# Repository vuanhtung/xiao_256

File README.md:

# xiao_256

Split keyboard with 5 rows & 6 columns on each half (hence the name 2 * 5 * 6) using xiao ble mcu & gateron low profile switch.

The pcb is reversible. A small pcb is also available to cover the mcu, the battery, & the wiring.

zmk config is available at https://github.com/vuanhtung/zmk-config

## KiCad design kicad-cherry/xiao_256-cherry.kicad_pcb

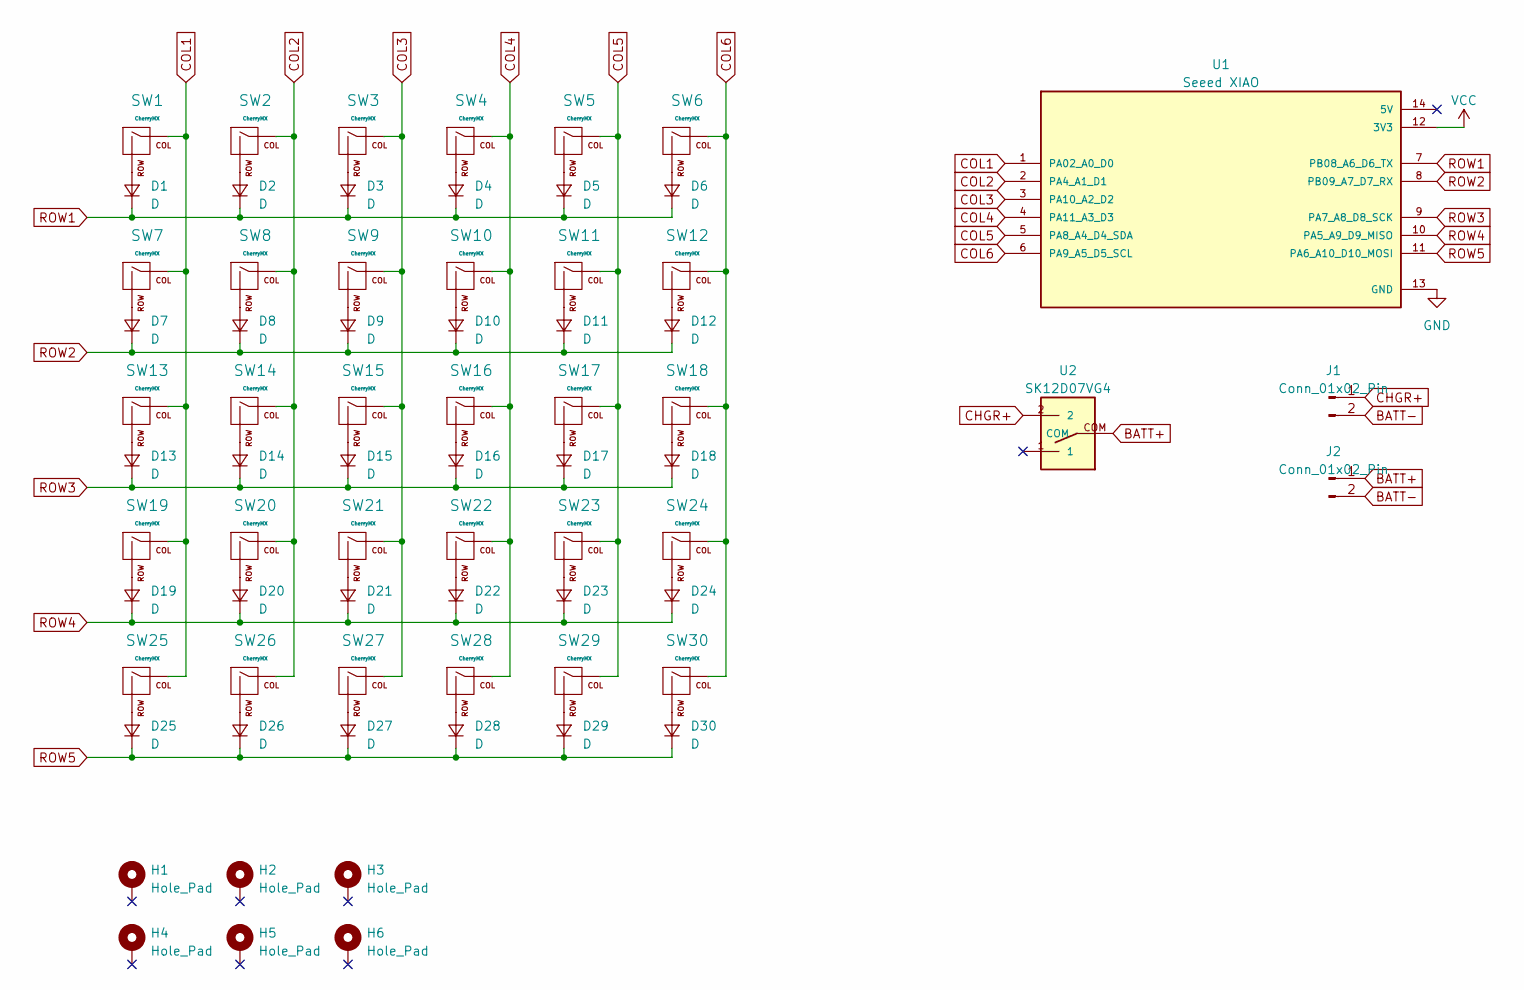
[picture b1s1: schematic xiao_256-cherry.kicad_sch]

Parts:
D1, D2, D3, D4, D5, D6, D7, D8, D9, D10, D11, D12, D13, D14, D15, D16, D17, D18, D19, D20, D21, D22, D23, D24, D25, D26, D27, D28, D29, D30: D; D_DO-35_SOD27_P7.62mm_Horizontal
H1, H2, H3, H4, H5, H6: Hole_Pad; Mount_M2
J1, J2: Conn_01x02_Pin; PinHeader_1x02_P2.54mm_Vertical
SW1, SW2, SW3, SW4, SW5, SW6, SW7, SW8, SW9, SW10, SW11, SW12, SW13, SW14, SW15, SW16, SW17, SW18, SW19, SW20, SW21, SW22, SW23, SW24, SW25, SW26, SW27, SW28, SW29, SW30: CherryMX; SW_MX_reversible
U1: Seeed XIAO; Seeed Xiao flip; PARTREV N/A
U2: SK12D07VG4

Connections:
BATT+: J2.1, U2.COM
BATT-: J1.2, J2.2
CHGR+: J1.1, U2.2
COL1: SW1.1 (COL), SW7.1 (COL), SW13.1 (COL), SW19.1 (COL), SW25.1 (COL), U1.1 (PA02_A0_D0)
COL2: SW2.1 (COL), SW8.1 (COL), SW14.1 (COL), SW20.1 (COL), SW26.1 (COL), U1.2 (PA4_A1_D1)
COL3: SW3.1 (COL), SW9.1 (COL), SW15.1 (COL), SW21.1 (COL), SW27.1 (COL), U1.3 (PA10_A2_D2)
COL4: SW4.1 (COL), SW10.1 (COL), SW16.1 (COL), SW22.1 (COL), SW28.1 (COL), U1.4 (PA11_A3_D3)
COL5: SW5.1 (COL), SW11.1 (COL), SW17.1 (COL), SW23.1 (COL), SW29.1 (COL), U1.5 (PA8_A4_D4_SDA)
COL6: SW6.1 (COL), SW12.1 (COL), SW18.1 (COL), SW24.1 (COL), SW30.1 (COL), U1.6 (PA9_A5_D5_SCL)
GND: U1.13 (GND)
unnamed: D1.2 (A), SW1.2 (ROW)
unnamed: D2.2 (A), SW2.2 (ROW)
unnamed: D3.2 (A), SW3.2 (ROW)
unnamed: D4.2 (A), SW4.2 (ROW)
unnamed: D5.2 (A), SW5.2 (ROW)
unnamed: D6.2 (A), SW6.2 (ROW)
unnamed: D7.2 (A), SW7.2 (ROW)
unnamed: D8.2 (A), SW8.2 (ROW)
unnamed: D9.2 (A), SW9.2 (ROW)
unnamed: D10.2 (A), SW10.2 (ROW)
unnamed: D11.2 (A), SW11.2 (ROW)
unnamed: D12.2 (A), SW12.2 (ROW)
unnamed: D13.2 (A), SW13.2 (ROW)
unnamed: D14.2 (A), SW14.2 (ROW)
unnamed: D15.2 (A), SW15.2 (ROW)
unnamed: D16.2 (A), SW16.2 (ROW)
unnamed: D17.2 (A), SW17.2 (ROW)
unnamed: D18.2 (A), SW18.2 (ROW)
unnamed: D19.2 (A), SW19.2 (ROW)
unnamed: D20.2 (A), SW20.2 (ROW)
unnamed: D21.2 (A), SW21.2 (ROW)
unnamed: D22.2 (A), SW22.2 (ROW)
unnamed: D23.2 (A), SW23.2 (ROW)
unnamed: D24.2 (A), SW24.2 (ROW)
unnamed: D25.2 (A), SW25.2 (ROW)
unnamed: D26.2 (A), SW26.2 (ROW)
unnamed: D27.2 (A), SW27.2 (ROW)
unnamed: D28.2 (A), SW28.2 (ROW)
unnamed: D29.2 (A), SW29.2 (ROW)
unnamed: D30.2 (A), SW30.2 (ROW)
ROW1: D1.1 (K), D2.1 (K), D3.1 (K), D4.1 (K), D5.1 (K), D6.1 (K), U1.7 (PB08_A6_D6_TX)
ROW2: D7.1 (K), D8.1 (K), D9.1 (K), D10.1 (K), D11.1 (K), D12.1 (K), U1.8 (PB09_A7_D7_RX)
ROW3: D13.1 (K), D14.1 (K), D15.1 (K), D16.1 (K), D17.1 (K), D18.1 (K), U1.9 (PA7_A8_D8_SCK)
ROW4: D19.1 (K), D20.1 (K), D21.1 (K), D22.1 (K), D23.1 (K), D24.1 (K), U1.10 (PA5_A9_D9_MISO)
ROW5: D25.1 (K), D26.1 (K), D27.1 (K), D28.1 (K), D29.1 (K), D30.1 (K), U1.11 (PA6_A10_D10_MOSI)
VCC: U1.12 (3V3)

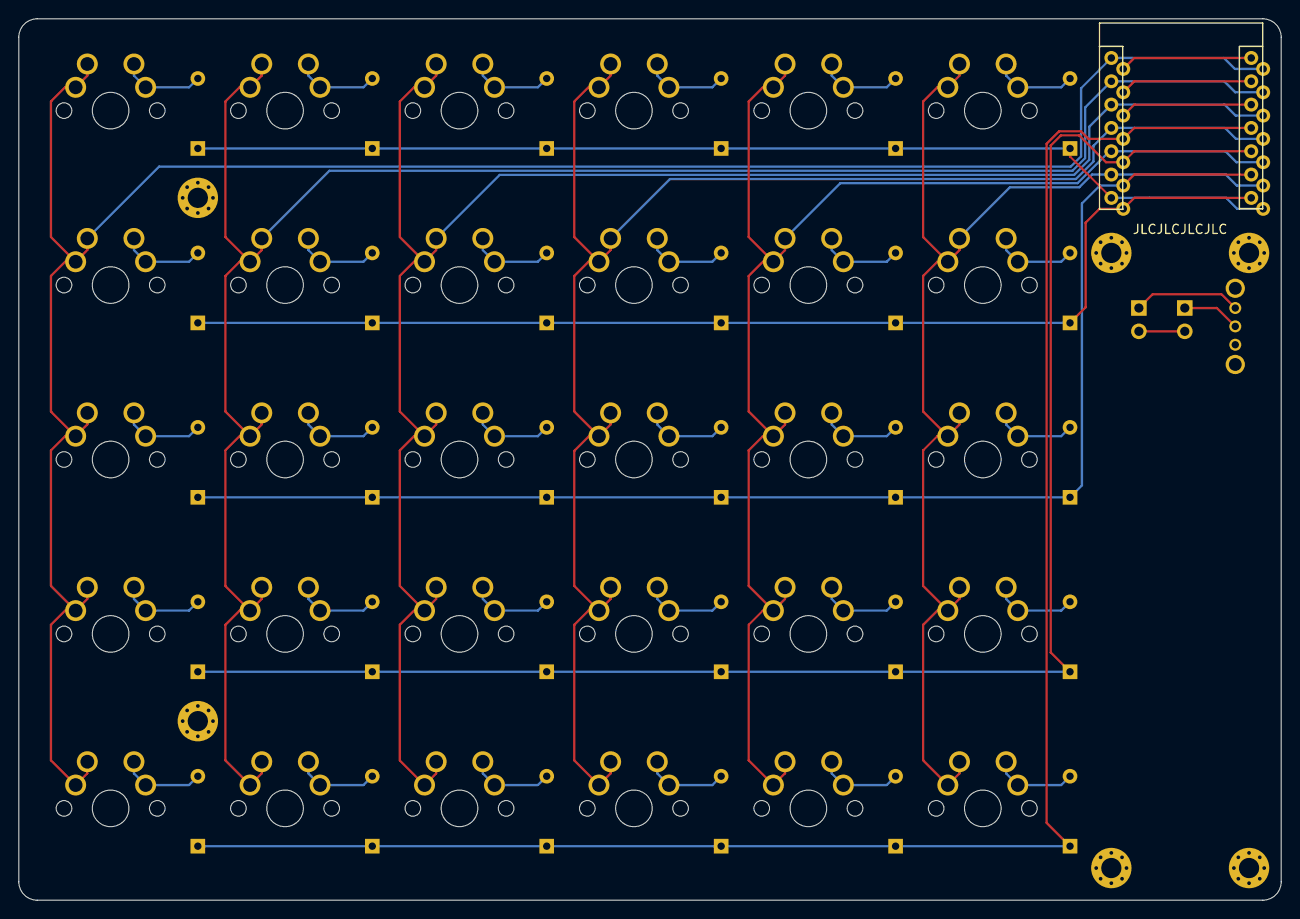
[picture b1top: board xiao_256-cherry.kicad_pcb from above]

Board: 2 copper layers, 137.5 x 96.0 mm, 70 parts (0 on the bottom side), 44 nets.

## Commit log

2023-04-12 start xiao_256
2023-04-13 finish routing
2023-04-13 gerber, not done yet
2023-04-13 add cover, tweak footprints
2023-04-14 gerber ready
2023-04-14 make cover symmetric
2023-05-04 add pictures
2023-05-04 add zmk config link
2023-10-22 add support for cherry mx
2023-10-22 finish routing cherry mx
2023-10-22 add gerber for cherry
